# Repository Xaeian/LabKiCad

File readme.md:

_Repozytorium stanowi element warsztatów z projektowania urządzeń elektronicznych i celowo nie zawiera postępów realizacji prac._

## KiCad _"od koncepcji do gotowego urządzenia"_

KiCad jest w zasadzie zbiorem programów, których ogólnym przeznaczeniem jest projektowanie obwodów drukowanych na płytkach PCB.

W pakiet KiCad wchodzą:

- **eeschema** - Program do rysowania schematów
- **pcbnew** - Program do projektowania PCB (rozmieszczanie elementów i realizacja połączeń)
- **gerbview** - Program do przeglądania plików produkcyjnych GERBER
- **bitmap2component** - Program konwertujący obraz `.bmp` oraz `.jpg` na komponent dostępny z poziomu **pcbnew**
- **pcb_calculator** - Programik pomocny w często wykonywanych obliczeniach
- **pl_editor** - Edytor ramek dla **eeschema** oraz **pcbnew**

Programy dobrze z sobą współpracują, jednak nadal są oddzielnymi bytami, które mogą być wykorzystywane niezależnie lub z innymi programami. Taka koncepcja sprawia, że rozwiązania które **KiCad** wykorzystuje, wydają się przekombinowane względem sandbox'owego **Eagle** czy **Altium Designer**.

## Biblioteki

Na początek warto korzystać z bibliotek instalowanych razem z programem, jednak im dłużej pracujemy z programem KiCad, tym więcej komponentów będziemy tworzyli samodzielnie lub dodawali z internetu. 

_Koniec końców po 5 latach pracy z wywalimy wszystkie standardowe biblioteki i sami zrobimy z tym porządek. U mnie tak się stało, kiedy KiCad przeszedł z wersji `4` do `5` i w związku ze zmianą struktur bibliotek wszystkie projekty mi się rozsypały._

Dlatego razem z kursem dołączona jest okrojona wersja bibliotek, która jest wystarczająca, żeby zrealizować prosty projekt przygotowany w kursie:

- `{URL}\liblary\Symbols\` - Biblioteki zawierające symbole;
  - Pliki w formacie `.lib`;
- `{URL}\liblary\Footprints\` - Biblioteki zawierające footprint'y _(komponenty)_;
  - Pliki w formacie `.kicad_mod`;
- `{URL}\liblary\Models\` - Biblioteki zawierające modele 3D ;
  - Pliki w formacie `.step` lub `.wrl`.

Oczywiście `{URL}` jest lokalizacją, gdzie zostało sklonowane repozytorium z kursem. Wygodnie jest każdą z tych ścieżek dodać w programie jako ścieżkę względną:

- `LSB` - Ścieżka dostępu do bibliotek z symbolami
- `LFP` - Ścieżka dostępu do bibliotek komponentami
- `L3D` - Ścieżka dostępu do bibliotek z modelami 3D

Wówczas dodając bibliotekę, będziemy mogli odnosić się do utworzonych ścieżek. Biblioteki można dodawać z poziomu programu, jednak w dłuższej perspektywie praktyczniej jest edytować pliki za to odpowiedzialne.

Informacją jakie biblioteki **symboli** będą widoczne z poziomu programu **eeschema** określa się w pliku `sym-lib-table`.

Informacją jakie biblioteki **footprint'ów** będą widoczne z poziomu programu **pcbnew** określa się w pliku `fp-lib-table` w lokalizacji.

Oba pliki muszą znajdować się w lokalizacji:

    C:\Users\{USER}\AppData\Roaming\kicad

Zatem przed uruchomieniem programu udajmy się pod podaną lokalizację i przekopiujmy pliki `sym-lib-table` oraz `fp-lib-table` z folderu `{URL}\liblary\`.

Można też użyć przygotowanego skryptu `cp-lib-table.sh`:

```bash
NAME=$('whoami')
URL="C:/Users/$NAME/AppData/Roaming/kicad/"
FP=$URL"fp-lib-table"
SYM=$URL"sym-lib-table"
cp fp-lib-table $FP
cp sym-lib-table $SYM
```

## Koncepcja

Rysowanie schematów nie wydaje się trudne, nie mniej wymaga nieco wprawy, a przede wszystkim pomysłu. Musimy wiedzieć, co rysujemy lub projektujemy.

Załóżmy, że otrzymaliśmy zlecenie na projekt urządzenia, które ma migać diodą, z dostrajaną przez urzytkownika częstotliwością. Sposobów na realizację takiego projektu będzie przynajmniej kilka, ale my wykożystamy mikrokontroler, a dokładnie popularny układ `Atmega328P`.

Prostym sposobem na różnego rodzaju regulację jest wykorzystanie potencjometru oraz przetwornika `ADC`. Miganie diodą można zrealizować poprzez zmianę stanu na pinie i odczekanie pewnego odcinka czasu `_delay_ms(x)`, jednak bardziej elegancko będzie wykorzystać `PWM`. Jak co nieco pracowaliśmy z procesorami **AVR** lub **Arduino** to z [tą ściągawką](https://github.com/Xaeian/labs-avr#speedrun-avr) dobranie pinów nie powinno stanowić problemu. W przeciwnym wypadku podłączymy diodę i potencjometr do dowolnego pinu procesora.

Jak ktoś nie do końca wie jak podłączyć **mikrokontroler**, **potencjometr**, czy sterować **diodą LED** to poniższy rysunek powinien wyjaśnić sprawę.

W praktycznej implementacji można jeszcze dodać stabilizator **LDO** oraz złącze zasilania, np. **Power Jack** lub zwykłych zacisków śrubowych.

## Rysowanie schematu

Pora utworzyć nowy projekt i wejść do programu **eeschema**.

_Niektóre narzędzia nie są dostępne z poziomu pasków bocznych. Jest to nieznośne dla nowych użytkowników, gdyż niektóre z nich są niezbędne do efektywnego tworzenia schematów._

Na początek najlepiej dodać wszystkie wykorzystywane komponenty (`A`) oraz tagi zasilania (`P`). Porozmieszczać (`M`,`G`), a na koniec odpowiednio połączyć (`W`). Nie wykorzystywane wyprowadzenia mikrokontrolera oznaczyć krzyżykiem (`Q`). Ważne jest dobranie wartości elementów (`V`) oraz ponumerowanie _(nadanie referencji)_ (`U`). Gdy nie jest dla nas istotne, jaki komponent będzie miał jaki numer, możemy skorzystać z numerowania automatycznego:

Jeżeli chcemy korzystać z kontroli błędów, konieczne jest połączenie symboli zasilania z symbolami _flag_. Wówczas program ma informacje, które ze ścieżek doprowadzają zasilanie.

Poza uzupełnieniem wartości _(**Value**)_ oraz oznaczeniem _(**Reference**)_ konieczne jest przypisanie **Footprint**'u do symboli. Można zrobić to poprzez edycje pól dla każdego symbolu z osobna (`E`) lub globalnie _(toolbar)_.

Do każdego symbolu możemy wskazać link do dokumentacji _(**Datasheet**)_. Pozostałe pola: **Manufacturer**, **Code**, **Supplier**, **Description** standardowo nie występują w programie KiCad, jednak są bardzo użyteczne, ponieważ w sytuacji, gdy montaż urządzenia będzie wykonywał ktoś inny, pozwalają precyzyjnie określić, jaki element ma zostać zamówiony, gdzie można go kupić oraz czym się kierować podczas doboru zamienników.

_Footprint'y możemy również przypisywać za pomocą dedykowanej do tego aplikacji, lecz w moim subiektywnym odczuciu narzędzie _"edycja pól symboli"_ jest równie praktyczne._

Elementów możemy szukać u dystrybutorów:
- [TME](https://www.tme.eu/pl/);
- [Mouser](https://pl.mouser.com/);
- [Digikey](https://www.digikey.pl/);
- [Farnel](https://pl.farnell.com/);
- [Maritex](https://www.maritex.com.pl/);

oraz bezpośrednio u producentów:
- [ST Microelectronic](https://www.st.com/);
- [Texas Instruments](https://www.ti.com/);
- [Microchip](https://www.microchip.com/);
- [Infineon](https://www.microchip.com/);
- [Vishay](https://www.vishay.com/);
- [Diodes Incorporated](https://www.diodes.com/);
- [Würth Elektronik](https://www.we-online.com/catalog/en).

## Projektowanie PCB

Na koniec zabawy ze schematem należy wygenerować listę sieci _(**netlist**)_, przejść do programu **pcbnew**, a następnie załadować wygenerowaną listę `.net`.

Wszystkie dobrane na etapie rysowania schematu komponenty powinny rozsypać się w oknie roboczym. Zanim jednak przejdziemy do projektowania dobrze ustawić reguły projektowe, takie jak grubości ścieżek i rozmiary przelotek.

Ustawienia z grafiki wyżej są odpowiednie dla wykonywania budżetowych płytek w firmach zajmujących się produkcją PCB. Gdy jednak byśmy chcieli płytkę wykonać samodzielnie, ścieżki powinny być grubsze, a odstępy większe.

Jednak płytki PCB to nie tylko miedziane ścieżki i miejsca, gdzie miedź została wytrawiona lub zdrapana. Dlatego w programie mamy do czynienia z warstwami _(**layers**)_

Warstwy z przedrostkiem `F.` odnoszą się do górnej _(Top)_ strony płytki, natomiast `B.` do dolnej _(Bottom)_.
Podczas stawiania pierwszych kroków warstwy oznaczone na ilustracji jako **TIER2** można całkowicie zignorować:
- `F.Cu`, `B.Cu` - Warstwy miedzi;
- `F.Adhes`, `B.Adhes` - Warstwy kleju;
  - Gdy połączenie lutowane jest nie wystarczające, by mechanicznie utrzymać komponent;
- `F.Paste`, `B.Paste` - Warstwy dla pasty lutowniczej;
- `F.SilkS`, `B.SilkS` - Warstwy opisów na płytce;
- `F.Mask`, `B.Mask` - Warstwy pól lutowniczych;
  - Na tej warstwie nie zostanie umieszczona **soldermaska**;
- `Dwgs.User`, `Cmts.User` - Warstwy opisów dla urzytkownika
  - Dodatkowe informacje, takie jak wymiary;
- `Eco1.User`, `Eco2.User` - Warstwy bez przeznaczenia;
- `Edge.Cuts` - Warstwa krawędzi płytki oraz frezów;
- `F.CrtYd`, `B.CrtYd` - Warstwy zajętości komponentu;
  - Gdy warstwy zajętości różnych elementów nachodzą na siebie to kontrola błędów to wykryje;
- `F.Fab`, `B.Fab` - Warstwa montażowa;
  - Jest eksportowana jako dokumentacja montażowa;

Teraz wystarczy:
- wyznaczyć obrys płytki;
- wyznaczyć punkt początkowy płytki _(lewy-górny róg)_;
- rozstawić odpowiednio elementy;
- połączyć je zgodnie z sugestiami programu;
  - nie łączymy ścieżek GND;
- dodajemy otwory montażowe i grafikę;
- dodać strefy miedzi przyległą do GND _(**polygon**)_.

Brzmi prosto, ale takie nie jest! Na szczęście na koniec jesteśmy nagrodzeni widokiem 3D naszej płytki PCB wraz z zamontowanymi elementami (`Alt` + `3`). Jeśli jesteśmy zadowoleni z rezultatu, możemy wygenerować dokumentację produkcyjną, na którą składają się:
- `1.` Pliki **GERBER**
- `2.` Pliki wierceń
- `3.` Lista materiałowa **BOM**
- `4.` Dokumentacja montażowa
- `5.` Rozmieszczenie elementów **Pick&Place**

Gdy montaż realizujemy samodzielnie, wystarczy wykonać punkty `1` i `2`.
Punkt `5` konieczny jest jedynie przy dużej produkcji z zautomatyzowanym montażem.

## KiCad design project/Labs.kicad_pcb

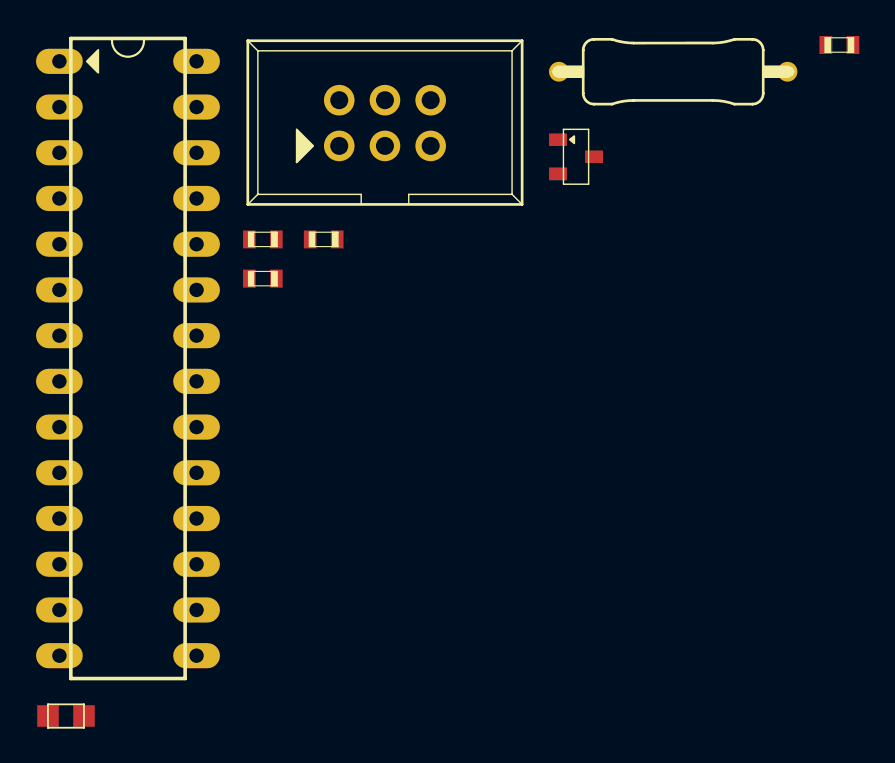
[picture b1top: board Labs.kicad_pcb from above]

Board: 2 copper layers, 9 parts (0 on the bottom side), 9 nets, no tracks yet.

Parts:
C1, C2, C3, C4: 15pF; 0603
IC1: ATMEGA328P; DIP28-M04
IC2: AP7381; SOT23-3
IDC1: IDC8; IDC6
R1: 20Ω; 0.5W
XTAL1: 16MHz; 2012

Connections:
GND: C1.2, C2.2, C3.2, C4.2, IC1.8, IC1.22, IC2.2, IDC1.6
unnamed: C1.1, IC1.10, XTAL1.1
unnamed: C2.1, IC1.9, XTAL1.2
unnamed: C4.1, IC1.7, IC1.20, IC1.21, IC2.3, R1.1
unnamed: IC1.17, IDC1.4
unnamed: IC1.18, IDC1.3
unnamed: IC1.19, IDC1.1
RST: IC1.1, IDC1.5, R1.2
VCC: C3.1, IC2.1

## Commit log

2021-09-21 init
2021-09-21 image-x4
2021-09-21 note-pre-final
2021-09-22 note-final
2021-09-23 liblary
2021-09-27 speedrun
2021-09-27 copy.sh
